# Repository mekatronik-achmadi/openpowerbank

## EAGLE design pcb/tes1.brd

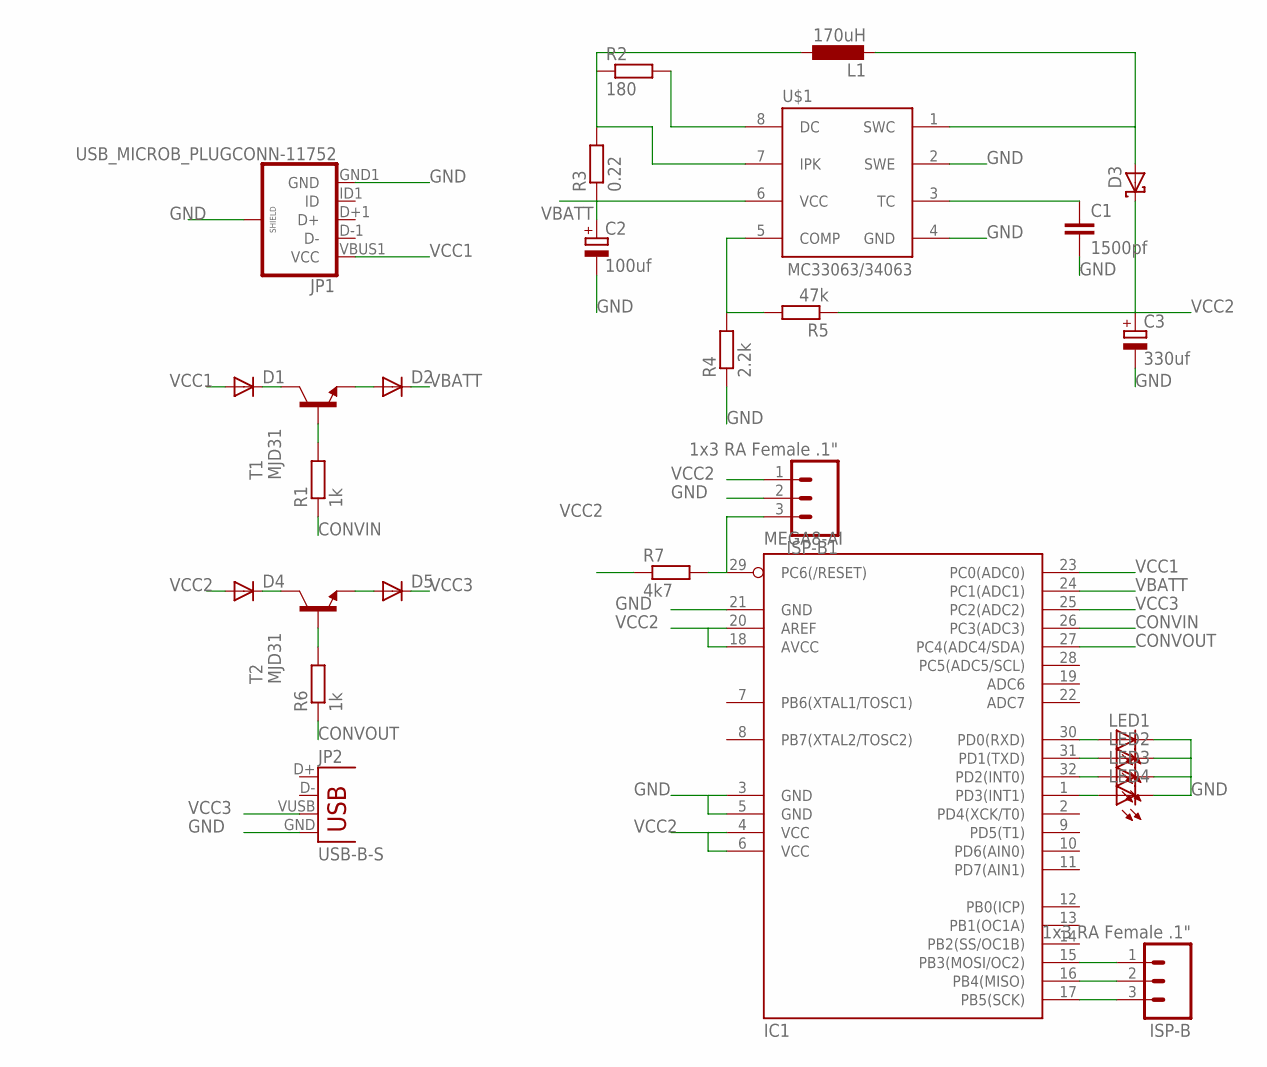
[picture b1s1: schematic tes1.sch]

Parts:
C1: 1500pf; C1206
C2: 100uf; 153CLV-1014
C3: 330uf; 153CLV-1014
D1, D2, D4, D5: DIODE-SMC; SMC
D3: SCHOTTKY-DIODEF126Z12; F126Z12
IC1: MEGA8-AI; TQFP32-08
ISP-B, ISP-B1: 1x3 RA Female .1"; 1X03_SMD_RA_FEMALE
JP1: USB_MICROB_PLUGCONN-11752; USB-B-MICRO-SMD_V03
JP2: USB-B-S; USB-B-SMT
L1: 170uH; L5650M
LED1, LED2, LED3, LED4: LEDSML1206; SML1206
R1, R6: 1k; R1206
R2: 180; R1206
R3: 0.22; R1206
R4: 2.2k; R1206
R5: 47k; R1206
R7: 4k7; R1206
T1, T2: MJD31; DPAK
U$1: MC33063/MC34063D; SO08

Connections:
CONVIN: IC1.26 (PC3(ADC3)), R1.1
CONVOUT: IC1.27 (PC4(ADC4/SDA)), R6.1
GND: C1.2, C2.-, C3.-, IC1.3 (GND), IC1.5 (GND), IC1.21 (GND), ISP-B1.2, JP1.GND1 (GND), JP1.SHIELD1 (SHIELD), JP1.SHIELD2 (SHIELD), JP1.SHIELD3 (SHIELD), JP2.GND, LED1.C, LED2.C, LED3.C, LED4.C, R4.1, U$1.2 (SWE), U$1.4 (GND)
unnamed: D1.C, T1.4 (C)
unnamed: C1.1, U$1.3 (TC)
unnamed: D2.A, T1.3 (E)
unnamed: L1.1, R2.1, R3.2, U$1.7 (IPK)
unnamed: R1.2, T1.1 (B)
unnamed: R2.2, U$1.8 (DC)
unnamed: R4.2, R5.2, U$1.5 (COMP)
unnamed: D4.C, T2.4 (C)
unnamed: D3.A, L1.2, U$1.1 (SWC)
unnamed: D5.A, T2.3 (E)
unnamed: R6.2, T2.1 (B)
unnamed: IC1.29 (PC6(/RESET)), ISP-B1.3, R7.2
unnamed: IC1.17 (PB5(SCK)), ISP-B.3
unnamed: IC1.16 (PB4(MISO)), ISP-B.2
unnamed: IC1.15 (PB3(MOSI/OC2)), ISP-B.1
unnamed: IC1.1 (PD3(INT1)), LED4.A
unnamed: IC1.32 (PD2(INT0)), LED3.A
unnamed: IC1.31 (PD1(TXD)), LED2.A
unnamed: IC1.30 (PD0(RXD)), LED1.A
VBATT: C2.+, D2.C, IC1.24 (PC1(ADC1)), R3.1, U$1.6 (VCC)
VCC1: D1.A, IC1.23 (PC0(ADC0)), JP1.VBUS1 (VCC)
VCC2: C3.+, D3.C, D4.A, IC1.4 (VCC), IC1.6 (VCC), IC1.18 (AVCC), IC1.20 (AREF), ISP-B1.1, R5.1, R7.1
VCC3: D5.C, IC1.25 (PC2(ADC2)), JP2.VUSB (VBUS)

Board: 2 copper layers, 28 parts (0 on the bottom side), 26 nets, no tracks yet.

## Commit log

2015-02-10 PCB schematic done
2015-02-10 ready to manufactured

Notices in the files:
parts and their libraries:
SparkFun-Connectors: Licensing: Creative Commons ShareAlike 4.0 International - https://creativecommons.org/licenses/by-sa/4.0
